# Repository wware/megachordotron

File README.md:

The Megachordotron
====

The Megachordotron is a
[MIDI controller](https://en.wikipedia.org/wiki/MIDI_controller)
organized around simple
[chords](https://en.wikipedia.org/wiki/Chord_(music)). It's
intended for people (like myself) who are too clumsy to play a guitar.

Since it's just a MIDI controller, it needs a
[MIDI synthesizer](https://en.wikipedia.org/wiki/MIDI#Synthesizers) to work.
The synthesizer is the PC on this little rack, which is a
[Linux Mint](https://www.linuxmint.com/) box running Fluidsynth (here is
[some](https://wiki.archlinux.org/index.php/FluidSynth)
[info](http://tedfelix.com/linux/linux-midi.html) about that).
There is also a guitar amp and a keyboard and monitor.

After Maker Faire is over, I want to spend some time making the synth much
[less cumbersome](http://www.tomsguide.com/us/best-mini-pcs,review-2760.html).
As it stands it is quite inconvenient.

BTW, the shortened URL for this repository is https://git.io/vPt04.

Printed circuit board
----

I use Cadsoft Eagle for PCB layout. For these designs you'll need to pick up
some third-party libraries.

* [Teensy 3.0 library](https://forum.pjrc.com/attachment.php?attachmentid=184&d=1358973338)
  - [Discussion of Teensy library](https://www.pjrc.com/teensy/eagle_lib.html)
* [Sparkfun Connector library](https://github.com/sparkfun/SparkFun-Eagle-Libraries)

Errata
----

I laid out the board in haste and made a mistake. One end of the diode D1 does not
connect correctly to the resistor R3. I think it's the cathode. I had to solder a
little jumper.

This board was originally used for a different instrument (hence the filename) and
the audio circuitry is not needed in the current instantiation. There is no need to
populate the TPA3122 (IC6) or the emitter follower to the left, or the parts around
them, or the last CD4051 (IC5). There is also no need to supply +12V or +5V other
than what is supplied by the USB cable.

The bypass caps should all be populated, and D1 and R3 must be populated.

Programming the Teensy
----

You should use a Teensy 3.1 or 3.2 to build the Megachordotron.

In the Arduino application menu, choose `Tools > USB Type`, and select `MIDI`.

I am running my Teensy at 72 MHz, but that's probably something you can experiment
with. There is only one place in the code where fast timing is really significant,
in the `read_kdy` function in `teensy.ino` which is mostly in assembly language.
Actually now that I think of it, I'll probably switch to 96 MHz, because that
affects keyboard sensitivity.

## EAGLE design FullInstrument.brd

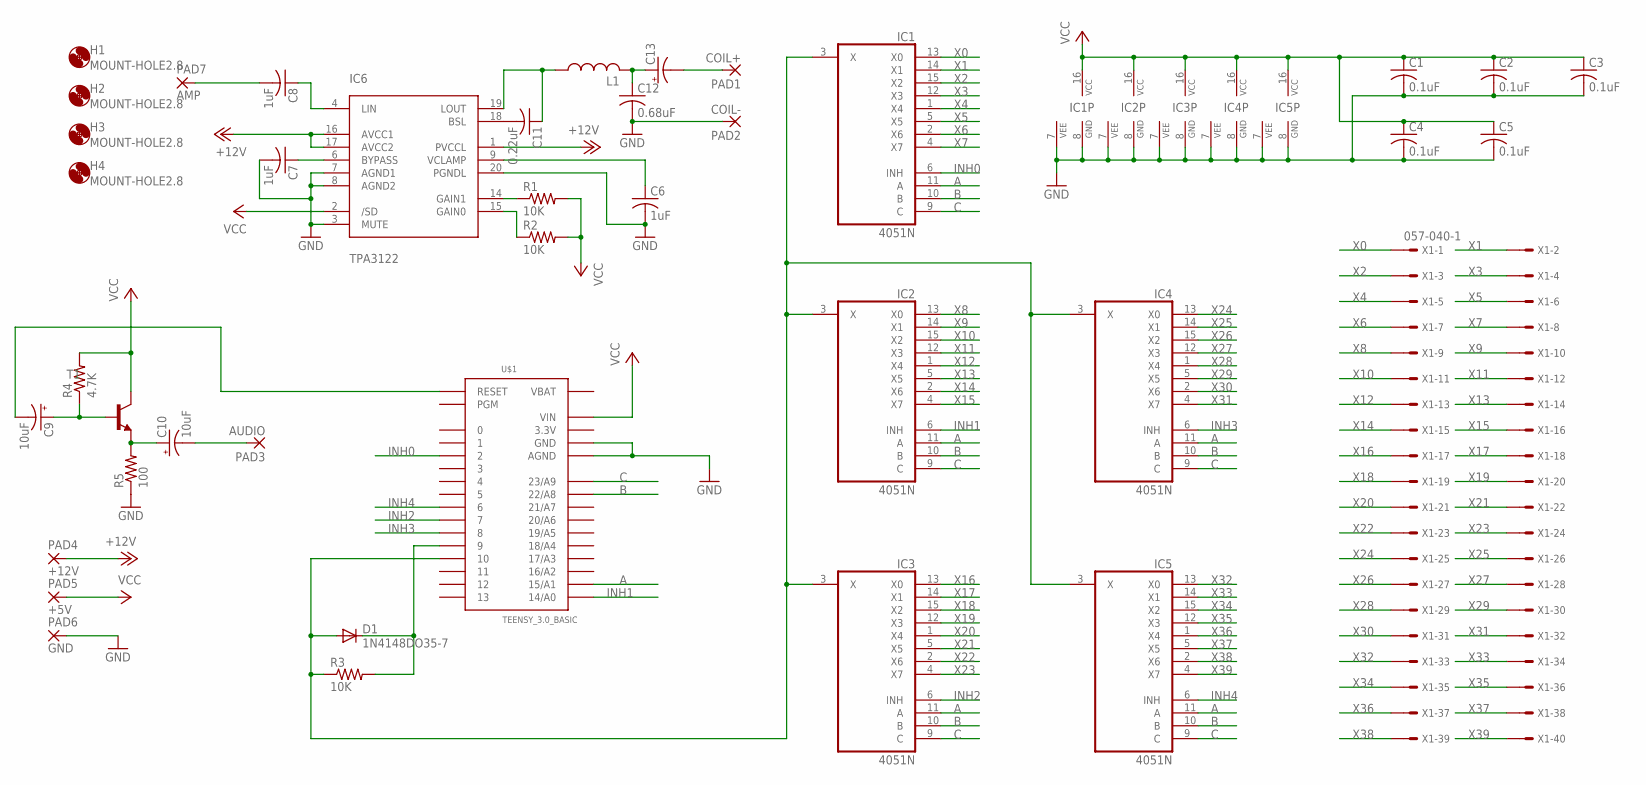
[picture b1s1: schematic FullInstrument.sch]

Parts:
C1, C2, C3, C4, C5: 0.1uF; C025-025X050
C6, C7, C8: 1uF; C050-025X075
C9, C10: 10uF; E2-5
C11: 0.22uF; C050-025X075
C12: 0.68uF; C050-025X075
C13: CPOL-USE5-8.5; E5-8,5
D1: 1N4148DO35-7; DO35-7
H1, H2, H3, H4: MOUNT-HOLE2.8; 2,8
IC1, IC2, IC3, IC4, IC5: 4051N; DIL16
IC6: TPA3122; TPA3122-DIP20
L1: L-US6000-XXX-RC; 6000-XXXX-RC
PAD1: COIL+; 3,17/1,3
PAD2: COIL-; 3,17/1,3
PAD3: AUDIO; 3,17/1,3
PAD4: +12V; 3,17/1,3
PAD5: +5V; 3,17/1,3
PAD6: GND; 3,17/1,3
PAD7: AMP; 3,17/1,3
R1, R2, R3: 10K; 0204V
R4: 4.7K; 0204V
R5: 100; 0204V
T1: -NPN-TO92-EBC; TO92-EBC
U$1: TEENSY_3.0_BASIC
X1: 057-040-1

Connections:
3.3V: U$1.3.3V, U$1.3.3V1 (3.3V)
+12V: IC6.1 (PVCCL), IC6.16 (AVCC1), IC6.17 (AVCC2), PAD4.1
A: IC1.11 (A), IC2.11 (A), IC3.11 (A), IC4.11 (A), IC5.11 (A), U$1.15/A1
B: IC1.10 (B), IC2.10 (B), IC3.10 (B), IC4.10 (B), IC5.10 (B), U$1.22/A8
C: IC1.9 (C), IC2.9 (C), IC3.9 (C), IC4.9 (C), IC5.9 (C), U$1.23/A9
GND: C1.2, C2.2, C3.2, C4.2, C5.2, C6.2, C7.2, C12.2, IC1.7 (VEE), IC1.8 (GND), IC2.7 (VEE), IC2.8 (GND), IC3.7 (VEE), IC3.8 (GND), IC4.7 (VEE), IC4.8 (GND), IC5.7 (VEE), IC5.8 (GND), IC6.3 (MUTE), IC6.7 (AGND1), IC6.8 (AGND2), IC6.20 (PGNDL), PAD2.1, PAD6.1, R5.1, U$1.AGND, U$1.GND, U$1.GND1 (GND)
INH0: IC1.6 (INH), U$1.2
INH1: IC2.6 (INH), U$1.14/A0
INH2: IC3.6 (INH), U$1.7
INH3: IC4.6 (INH), U$1.8
INH4: IC5.6 (INH), U$1.6
unnamed: IC6.14 (GAIN1), R1.1
unnamed: C11.2, IC6.18 (BSL)
unnamed: IC6.15 (GAIN0), R2.1
unnamed: C8.1, IC6.4 (LIN)
unnamed: C7.1, IC6.6 (BYPASS)
unnamed: C6.1, IC6.9 (VCLAMP)
unnamed: R3.2, U$1.9
unnamed: D1.A, IC1.3 (X), IC2.3 (X), IC3.3 (X), IC4.3 (X), IC5.3 (X), R3.1, U$1.10
unnamed: C10.+, R5.2, T1.E
unnamed: C9.+, R4.1, T1.B
unnamed: C11.1, IC6.19 (LOUT), L1.1
unnamed: C9.-, U$1.RESET
unnamed: C12.1, C13.+, L1.2
unnamed: C13.-, PAD1.1
unnamed: C10.-, PAD3.1
unnamed: C8.2, PAD7.1
VBAT: U$1.VBAT
VCC: C1.1, C2.1, C3.1, C4.1, C5.1, IC1.16 (VCC), IC2.16 (VCC), IC3.16 (VCC), IC4.16 (VCC), IC5.16 (VCC), IC6.2 (/SD), PAD5.1, R1.2, R2.2, R4.2, T1.C, U$1.VIN
X0: IC1.13 (X0), X1.1
X1: IC1.14 (X1), X1.2
X2: IC1.15 (X2), X1.3
X3: IC1.12 (X3), X1.4
X4: IC1.1 (X4), X1.5
X5: IC1.5 (X5), X1.6
X6: IC1.2 (X6), X1.7
X7: IC1.4 (X7), X1.8
X8: IC2.13 (X0), X1.9
X9: IC2.14 (X1), X1.10
X10: IC2.15 (X2), X1.11
X11: IC2.12 (X3), X1.12
X12: IC2.1 (X4), X1.13
X13: IC2.5 (X5), X1.14
X14: IC2.2 (X6), X1.15
X15: IC2.4 (X7), X1.16
X16: IC3.13 (X0), X1.17
X17: IC3.14 (X1), X1.18
X18: IC3.15 (X2), X1.19
X19: IC3.12 (X3), X1.20
X20: IC3.1 (X4), X1.21
X21: IC3.5 (X5), X1.22
X22: IC3.2 (X6), X1.23
X23: IC3.4 (X7), X1.24
X24: IC4.13 (X0), X1.25
X25: IC4.14 (X1), X1.26
X26: IC4.15 (X2), X1.27
X27: IC4.12 (X3), X1.28
X28: IC4.1 (X4), X1.29
X29: IC4.5 (X5), X1.30
X30: IC4.2 (X6), X1.31
X31: IC4.4 (X7), X1.32
X32: IC5.13 (X0), X1.33
X33: IC5.14 (X1), X1.34
X34: IC5.15 (X2), X1.35
X35: IC5.12 (X3), X1.36
X36: IC5.1 (X4), X1.37
X37: IC5.5 (X5), X1.38
X38: IC5.2 (X6), X1.39
X39: IC5.4 (X7), X1.40

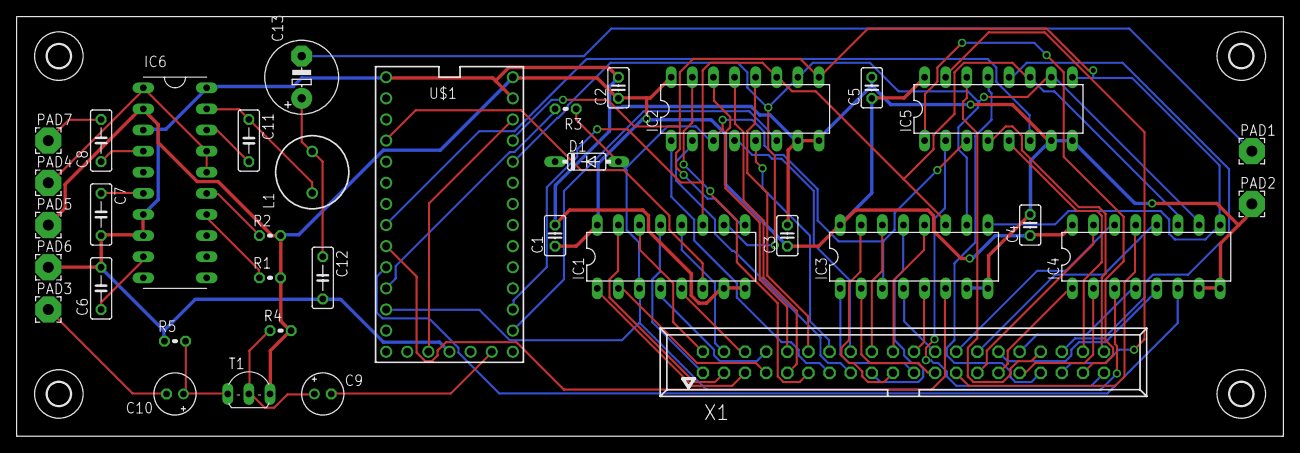
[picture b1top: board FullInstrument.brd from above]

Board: 2 copper layers, 152.4 x 50.5 mm, 40 parts (0 on the bottom side), 68 nets.

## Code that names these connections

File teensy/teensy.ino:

/**
 * Arduino/Teensy settings:
 *   Teensy 3.2 / 3.1
 *   USB Type: MIDI  (nothing additional)
 *   CPU Speed: 72 MHz
 */

extern unsigned char chord_table[];

#include "keys.h"

// Something is wonky about the eight high-numbered key connections
// on this PC board, probably some kind of assembly error, but the
// lower 32 are working OK.
#define NUM_KEYS 30

#define DIAGNOSTICS 0

#define PIANO            0
#define CELESTA         10
#define TUBULAR_BELLS   14
#define CHURCH_ORGAN    19
#define NYLON_GUITAR    24
#define CELLO           42
#define ORCHESTRAL_HARP 46
#define CHOIR_AAHS      52
#define TRUMPET         56
#define SYNTH_BRASS     62
#define ALTO_SAX        65
#define FLUTE           73

uint8_t voices[] = {
    PIANO, CELESTA, CHURCH_ORGAN, NYLON_GUITAR,
    CELLO, CHOIR_AAHS, TRUMPET, FLUTE
};

#define INH0  2
#define INH1  14
#define INH2  7
#define INH3  8
#define INH4  6

uint32_t inhibits[] = {INH0, INH1, INH2, INH3, INH4};

#define A_SELECT 15
#define B_SELECT 22
#define C_SELECT 23

/**
 * A pointer into chord_table, where we find the pitches for the sevn
 * strings.
 */
uint8_t *chord_pointer = &chord_table[7 * 6];

/**
 * If we want to transpose the chord up or down by some number of octaves,
 * do that here. This should be a multiple of 12.
 */
int8_t chord_transpose = 0;

// Port A, Port C, Port D
uint32_t port_settings[2 * NUM_KEYS];

#define PORT_A 0x400FF000
#define PORT_C 0x400FF080
#define PORT_D 0x400FF0C0

static inline uint32_t read_key(uint32_t X, uint32_t Y, uint32_t portc) {
    // offset 4 is set output
    // offset 8 is clear output
    // offset 16 is read input
    asm volatile(
        // digitalWrite(9, LOW);
        "mov %0, #0x08"                 "\n"
        "str %0, [%2, #8]"              "\n"

        // X = 20;
        "mov %0, #20"                   "\n"

        // while (X > 0) X--;
        "1:"                            "\n"
        "subs %0, %0, #1"               "\n"
        "bne 1b"                        "\n"

        // digitalWrite(9, HIGH);
        "mov %0, #0x08"                 "\n"
        "str %0, [%2, #4]"              "\n"

        // while (Y > 0) Y--;
        "2:"                            "\n"
        "subs %1, %1, #1"               "\n"
        "bne 2b"                        "\n"

        // X = digitalReadFast(10);
        "ldr %0, [%2, #16]"             "\n"
        "ands %0, %0, #0x10"            "\n"

        // digitalWrite(9, LOW);
        "mov %1, #0x08"                 "\n"
        "str %1, [%2, #8]"              "\n"
        : "+r" (X), "+r" (Y), "+r" (portc)
    );
    return !X;
}

void flash_int(int n)
{
    int i = n / 5;
    n -= 5 * i;
    while (i--) {
        digitalWrite(LED_BUILTIN, HIGH);
        delayMicroseconds(1000 * 1000);
        digitalWrite(LED_BUILTIN, LOW);
        delayMicroseconds(200 * 1000);
    }
    while (n--) {
        digitalWrite(LED_BUILTIN, HIGH);
        delayMicroseconds(200 * 1000);
        digitalWrite(LED_BUILTIN, LOW);
        delayMicroseconds(200 * 1000);
    }
}


int h = 0;

class Key : public BaseKey
{
public:
    Key(uint32_t _id) : BaseKey(_id) {}

    bool read_n(uint32_t n) {
        digitalWrite(A_SELECT, (id & 1) ? HIGH : LOW);
        digitalWrite(B_SELECT, (id & 2) ? HIGH : LOW);
        digitalWrite(C_SELECT, (id & 4) ? HIGH : LOW);
        unsigned int i;
        for (i = 0; i < 5; i++) {
            if (i == (id >> 3))
                digitalWrite(inhibits[i], LOW);
            else
                digitalWrite(inhibits[i], HIGH);
        }
        return read_key(0, n, PORT_C);
    }
};

class StringKey : public Key
{
public:
    StringKey(uint32_t _id) : Key(_id) {}

    /**
     * The pitch of the most recent key_down event.
     */
    int8_t last_pitch;

    void keydown(void) {
        int8_t pitch = chord_pointer[id];
        usbMIDI.sendNoteOn(pitch, 127, 1);
        last_pitch = pitch;
    }

    void keyup(void) {
        usbMIDI.sendNoteOff(last_pitch, 0, 1);
    }
};

Key *keyboard[NUM_KEYS];
uint8_t program;

KeySelect chord_base_select(6);
KeyGroup chord_modifier_group(0);
KeySelect program_select(0);

void setup() {
    uint8_t j;

    pinMode(LED_BUILTIN, OUTPUT);

    uint8_t i;

    pinMode(10, INPUT_PULLUP);
    pinMode(9, OUTPUT);
    digitalWrite(9, LOW);
    pinMode(2, OUTPUT);
    pinMode(6, OUTPUT);
    pinMode(7, OUTPUT);
    pinMode(8, OUTPUT);
    pinMode(14, OUTPUT);
    pinMode(15, OUTPUT);
    pinMode(22, OUTPUT);
    pinMode(23, OUTPUT);

    for (i = 0; i < NUM_KEYS; i++) {
        if (i < 7)
            keyboard[i] = new StringKey(i);
        else
            keyboard[i] = new Key(i);
    }

    for (i = 7; i < 19; i++)
        chord_base_select.add(keyboard[i]);
    for ( ; i < 22; i++)
        chord_modifier_group.add(keyboard[i]);
    for ( ; i < 30; i++)
        program_select.add(keyboard[i]);

    for (i = 0; i < NUM_KEYS; i++) {
        keyboard[i]->fresh_calibrate();
    }

    for (j = 0; j < 3; j++) {
        for (i = 0; i < NUM_KEYS; i++) {
            keyboard[i]->calibrate();
        }
    }

    program = 0;
    for (i = 0; i < 5; i++) {
        usbMIDI.sendProgramChange(voices[program], 1);
        delayMicroseconds(100 * 1000);
    }
}

void loop(void) {
    int i;

    for (i = 7; i < NUM_KEYS; i++)
        keyboard[i]->check();

    chord_base_select.scan();
    chord_modifier_group.scan();
    program_select.scan();

    int8_t cbs = chord_base_select.any_pressed();
    int8_t cmg = chord_modifier_group.any_pressed();
    int8_t ps = program_select.any_pressed();

    /*
     * 1 means major, 2 means minor, 4 means maj7, 6 means min7.
     * The value ends up always being even so we can right-shift
     * and use a smaller lookup table.
     */
    static int8_t modifier = 1;

    switch (chord_modifier_group.value()) {
        default:
        case 0:
        case 3:
        case 5:
        case 7:
            break;
        case 1:
            modifier = 1;
            break;
        case 2:
            if (modifier != 6)
                modifier = 2;
            break;
        case 4:
            if (modifier != 6)
                modifier = 4;
            break;
        case 6:
            modifier = 6;
            break;
    }

    if (cbs || cmg) {
        uint8_t *new_chord_pointer = &chord_table[
            7 * (
                12 * (modifier >> 1) + chord_base_select.value()
            )
        ];

        if (new_chord_pointer != chord_pointer) {
            chord_pointer = new_chord_pointer;
            for (i = 0; i < 7; i++) {
                if (keyboard[i]->state &&
                    chord_pointer[i] != ((StringKey*)keyboard[i])->last_pitch) {
                    keyboard[i]->keyup();
                    keyboard[i]->keydown();
                }
            }
        }
    }

    // select the instrument
    if (ps && !program_select.previous_pressed()) {
        digitalWrite(LED_BUILTIN, HIGH);
        int8_t p = program_select.value();
        if (p != program) {
            usbMIDI.sendProgramChange(voices[p], 1);
            program = p;
        }
    }
    else digitalWrite(LED_BUILTIN, LOW);

    chord_base_select.update();
    chord_modifier_group.update();
    program_select.update();

    for (i = 0; i < 7; i++)
        keyboard[i]->check();
}

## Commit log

2016-09-23 Updates - this is no longer the Tooba
2016-09-23 More README
2016-09-28 Refactor chord modifier group, clean up code.
2016-10-01 Add pictures, and a shortened URL.
2016-10-01 Add some links.
2016-10-02 Youtube video link
2016-10-03 Gerber and drill files for PC board
